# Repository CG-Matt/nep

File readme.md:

# Nano EEPROM Programmer

An Arduino Nano based 28C series EEPROM programmer

This reposity contains the software and firmware required to use the Nano EEPROM Programmer

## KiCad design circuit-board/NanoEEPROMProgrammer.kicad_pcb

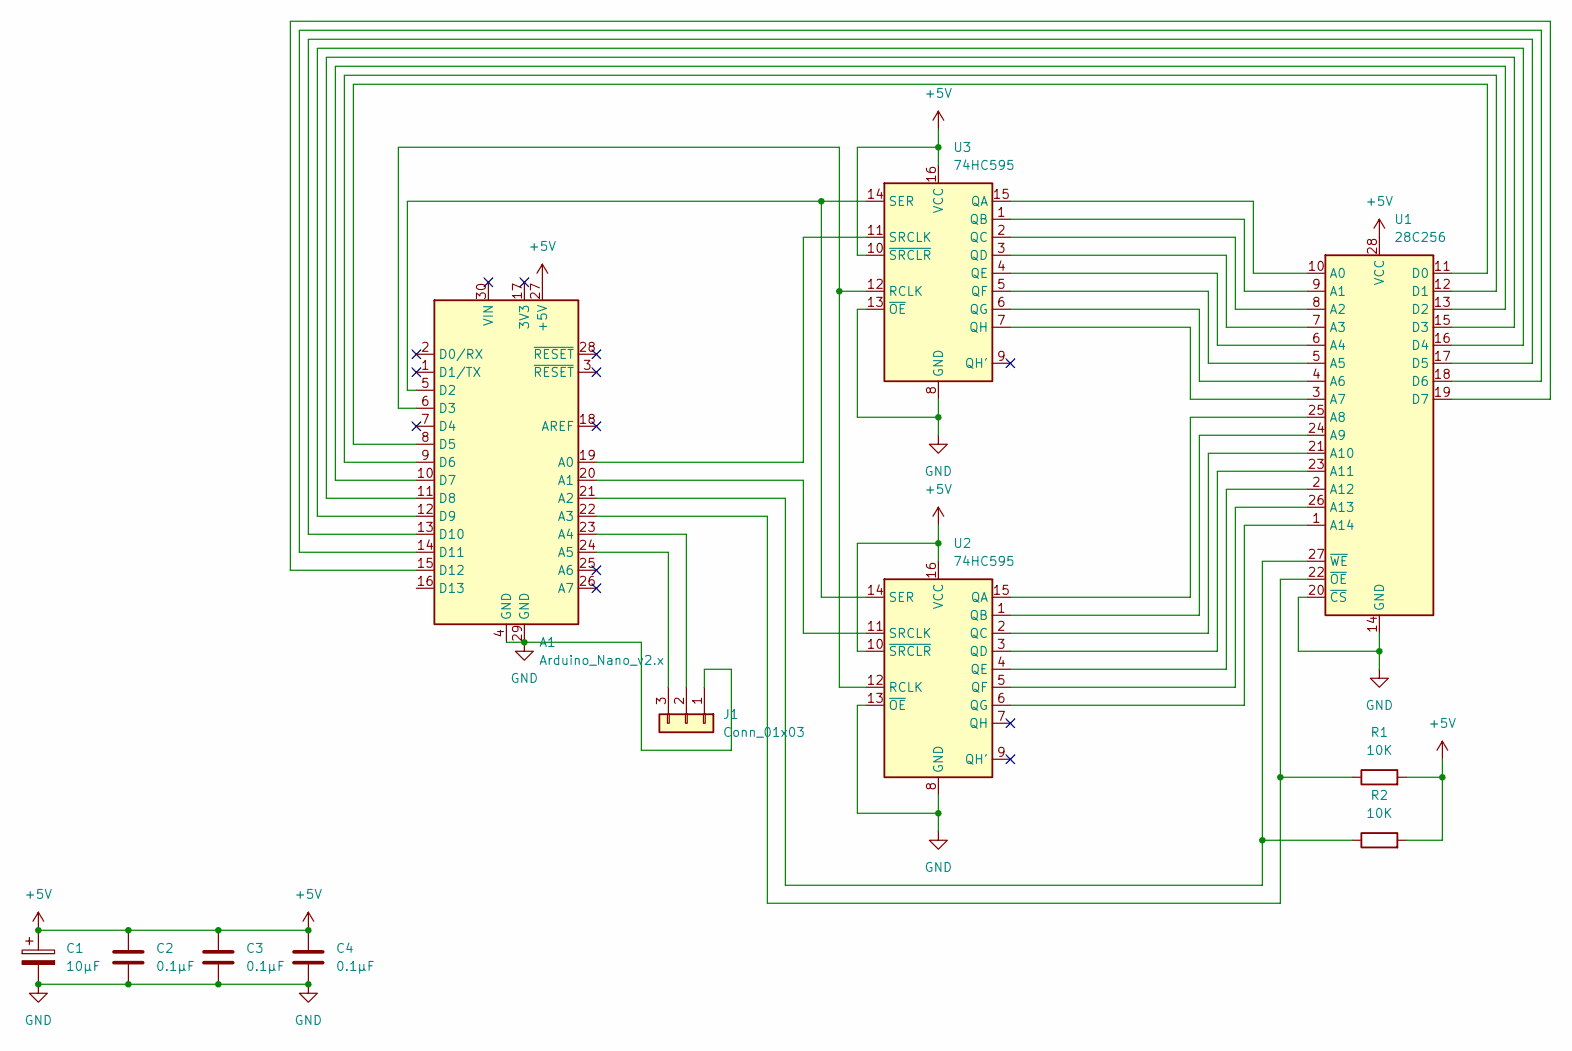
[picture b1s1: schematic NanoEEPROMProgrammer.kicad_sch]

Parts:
A1: Arduino_Nano_v2.x; Arduino_Nano
C1: 10µF; C_Radial_D5.0mm_H11.0mm_P2.00mm
C2, C3, C4: 0.1µF; C_Disc_D7.5mm_W2.5mm_P5.00mm
J1: Conn_01x03; PinSocket_1x03_P2.54mm_Vertical
R1, R2: 10K; R_Axial_DIN0207_L6.3mm_D2.5mm_P10.16mm_Horizontal
U1: 28C256; DIP_Socket-28_W11.9_W12.7_W15.24_W17.78_W18.5_3M_228-1277-0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
U2, U3: 74HC595; DIP-16_W7.62mm_Socket_LongPads

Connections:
+5V: A1.27 (+5V), C1.1, C2.1, C3.1, C4.1, R1.2, R2.2, U1.28 (VCC), U2.10 (~SRCLR), U2.16 (VCC), U3.10 (~SRCLR), U3.16 (VCC)
GND: A1.4 (GND), A1.29 (GND), C1.2, C2.2, C3.2, C4.2, J1.1, U1.14 (GND), U1.20 (~CS), U2.8 (GND), U2.13 (~OE), U3.8 (GND), U3.13 (~OE)
unnamed: A1.5 (D2), U2.14 (SER), U3.14 (SER)
unnamed: A1.6 (D3), U2.12 (RCLK), U3.12 (RCLK)
unnamed: A1.8 (D5), U1.11 (D0)
unnamed: A1.9 (D6), U1.12 (D1)
unnamed: A1.10 (D7), U1.13 (D2)
unnamed: A1.11 (D8), U1.15 (D3)
unnamed: A1.12 (D9), U1.16 (D4)
unnamed: A1.13 (D10), U1.17 (D5)
unnamed: A1.14 (D11), U1.18 (D6)
unnamed: A1.15 (D12), U1.19 (D7)
unnamed: A1.19 (A0), U3.11 (SRCLK)
unnamed: A1.20 (A1), U2.11 (SRCLK)
unnamed: A1.21 (A2), R2.1, U1.27 (~WE)
unnamed: A1.22 (A3), R1.1, U1.22 (~OE)
unnamed: A1.23 (A4), J1.2
unnamed: A1.24 (A5), J1.3
unnamed: U1.1 (A14), U2.6 (QG)
unnamed: U1.2 (A12), U2.4 (QE)
unnamed: U1.3 (A7), U3.7 (QH)
unnamed: U1.4 (A6), U3.6 (QG)
unnamed: U1.5 (A5), U3.5 (QF)
unnamed: U1.6 (A4), U3.4 (QE)
unnamed: U1.7 (A3), U3.3 (QD)
unnamed: U1.8 (A2), U3.2 (QC)
unnamed: U1.9 (A1), U3.1 (QB)
unnamed: U1.10 (A0), U3.15 (QA)
unnamed: U1.21 (A10), U2.2 (QC)
unnamed: U1.23 (A11), U2.3 (QD)
unnamed: U1.24 (A9), U2.1 (QB)
unnamed: U1.25 (A8), U2.15 (QA)
unnamed: U1.26 (A13), U2.5 (QF)

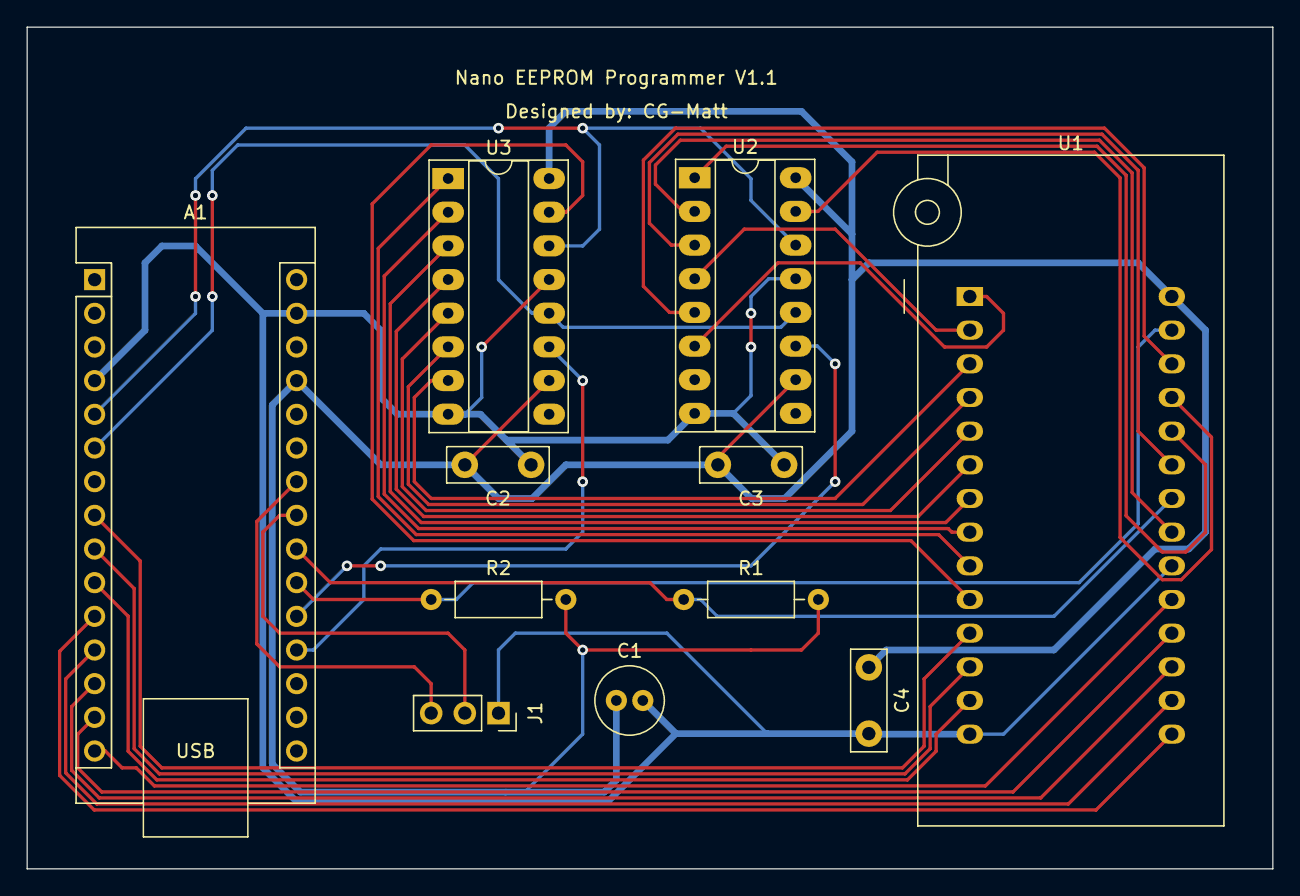
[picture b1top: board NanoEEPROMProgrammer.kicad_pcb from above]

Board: 2 copper layers, 94.0 x 63.5 mm, 11 parts (0 on the bottom side), 33 nets.

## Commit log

2024-08-22 Added SerialCommAwaitData Added a new function which will wait for any data to appear on the serial port until the timeout time is reached
2024-08-22 Added Handshakes file Added a text file outlining the handshake process between the Host and the device to either write to or read from the EEPROM
2024-08-22 Added false Added a define for false since true was already defined
2024-08-22 Added oflush Added a macro which flushed stdout using fflush
2024-08-22 Switch to SerialCommAwaitData Switched all cases where a while loop was being used to await data on the serial port to use SerialCommAwaitData instead. A few cosmetic and formatting changes were also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
2024-08-22 Added exit_code variable Added a global variable which gets returned upon exiting the program. It is used to set whether the program has exited successfully or if it had an error and exited because o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
2024-08-23 Added OpenFile Added a wrapper function for fopen which will also set exit_code if the file couldnt be open. Plus some small changes missed in previous commits.
2024-08-23 Improved Memory Management Added additional calls to free and fclose where it is necessary before exiting the program.
2024-08-23 Cosmetic Fixes Fixed some whitespace errors and changed an fprintf call to eprintf
2024-08-23 SerialCommApplyOptions returns value The SerialCommApplyOptions function now returns a value to signify success or failure to apply the options
2024-08-23 Added new read and write functions Added new SerialComm functions for reading and writing to a serial port from and to an external data buffer. Updated necessary functions accordingly
2024-08-23 OpenFile -> IntOpenFile Changed the name of the OpenFile function to not clash with the windows OpenFile function
2024-08-23 Added target win Added a windows target to the makefile
2024-08-23 Separated Platform dependent code Separated functions which call platform specific code
2024-08-23 Baudrate Defines Define windows baudrates in unix style
2024-09-07 Fixed SerialCommReadBytes Fixed accidentally passing a pointer to a pointer to the SerialCommBytesExt function. Fixed the function not returning the number of bytes read.
2024-09-07 Updated SerialCommSetBaudrate Set baudrate now uses more standard function provided by termios to change the baud rate.
2024-09-07 Added missing check for timeout SendImageSize was missing a check for a port timeout after sending data and awaiting status, this check has now been added.
2024-09-07 Cleaned up SerialCommAwaitStatus Cleaned up some of the code for SerialCommAwaitStatus
2024-10-05 Added SerialShiftOutU32 function Added a new function used to shift out a uint32_t over serial
2024-10-05 Updated SerialShiftInU32 function Changed the name of the shiftInU32 function to SerialShiftInU32. The function will now pull data directly from the Serial interface instead of combining data from a 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
2024-10-05 Made page buffer local The page buffer in which a transmitted page is received has now been made local to the handle_EEPROM_write function.
2024-10-05 Changed from if statements to switch case The if statements in the main loop function have been swapped out for switch case statements
2024-10-05 Cosmetic changes Added explanatory comments Fixed a typo Removed an empty line
2024-10-05 Updated firmware version Updated the firmware version to 0.1.1
2024-10-05 Added wait after port open Added a 2 second wait after a serial port is opened to allow the connected Arduino Nano to do its initialisation
2024-10-06 Reverted format string separation Reverted separating the format strings to be platform dependent. The code required mingw version 12 or higher to compile without warnings
2024-10-06 Better platform depended error logging Added PrintError macro which provides appropriate error logging depending on the compile target platform
2024-10-06 Removed debugging printf Removed a printf statement that was used for debugging purposes
2024-10-06 Cosmetic changes Changed "return -1" to "return EXIT_FAILURE"
2025-01-13 New help message Re-wrote the help message as it was created before the new argument parsing system and does not reflect the currently accepted argument format
2025-01-13 Error message prefix Added an "ERROR" prefix to all error messages
2025-01-13 Updates global variable names Prefixed all global variable names with "g_"
2025-10-24 Updated argument parser Updated the argument parser to take a pointer to the argument destination and return an int based on if the data was parser successfully or not
2026-05-20 Added Circuit Board Files Added circuit board files used for manufacturing the Arduino Nano EEPROM Programmer
